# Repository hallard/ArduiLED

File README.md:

AduiLED
=======

Arduino board for driving addressable RGB LED Strip with added nice features. 

Check out other projects on my [blog][1]

Detailed Description
====================

Everything is documented on this dedicated [post][2]

[1]: http://hallard.me
[2]: http://hallard.me/arduiled/

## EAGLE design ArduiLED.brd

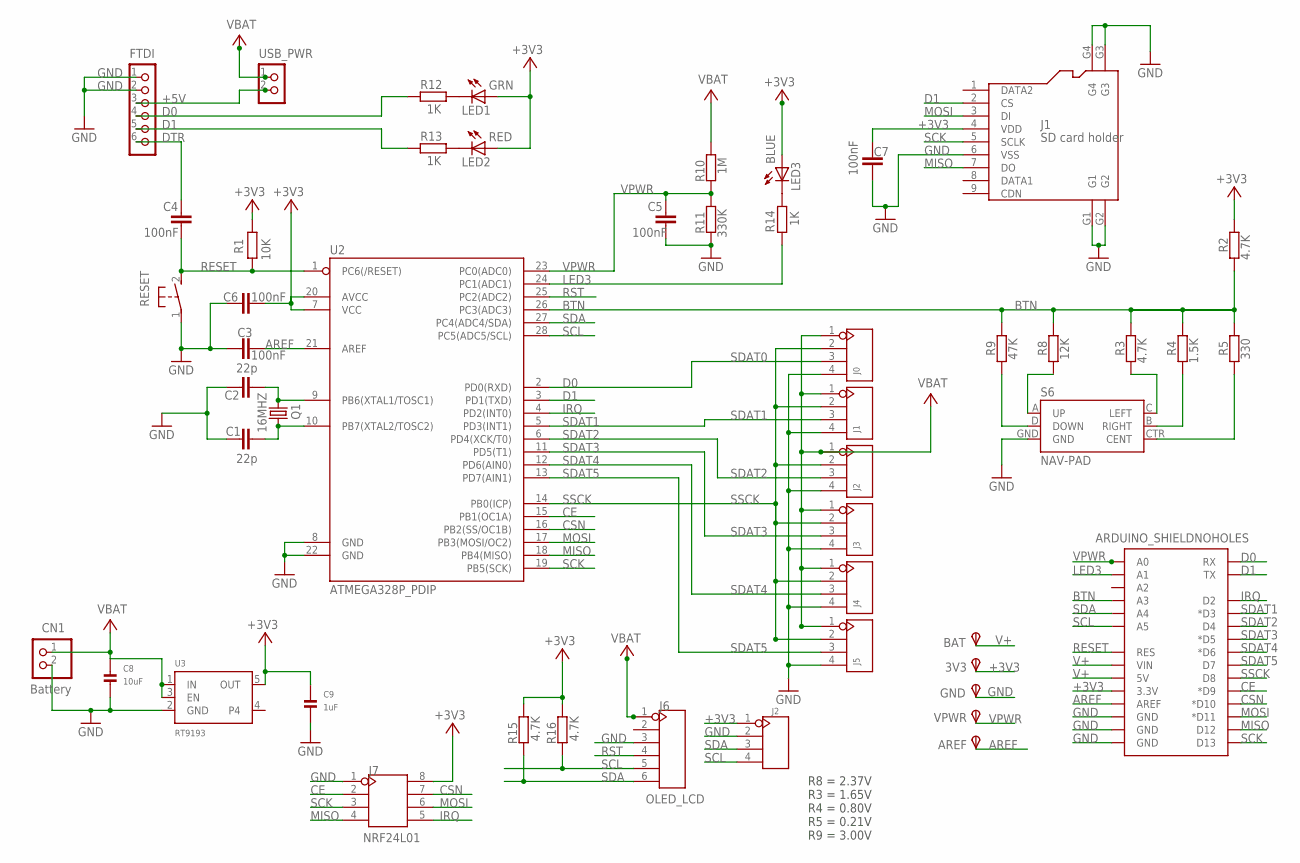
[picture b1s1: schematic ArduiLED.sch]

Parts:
3V3: TPSPAD1-13; P1-13
AREF: TPSPAD1-13; P1-13
BAT: TPSPAD1-13; P1-13
BRA: J2; 4P-2.54-80/40MIL
BRAS: J3; 4P-2.54-80/40MIL
C1, C2: 22p; C0805K
C3, C5, C6, C7: 100nF; C0805K
C4: 100nF; C0805
C8: 10uF; 0805
C9: 1uF; 0805
CN1: Battery; JST-PH-2-SMT-RA
D7: J5; 4P-2.54-80/40MIL
FTDI: CON_HEADER_1X06-PTH-RIGHT-ANGLED; M1X6_MALE_RIGHT_ANGLED
GND: TPSPAD1-13; P1-13
J1: SD card holder; 9P-SMD-W/-RING
J2: HEADER-4P-65/35MIL; 4P-65/35MIL
J6: OLED_LCD; 6P-2.54-65/35MIL
J7: NRF24L01; 2X4P-2.54
JAMB: J4; 4P-2.54-80/40MIL
LED1: GRN; LED-805
LED2: RED; LED-805
LED3: BLUE; LED-805
Q1: 16MHZ; HC49U-V
R1: 10K; M0805
R2, R3, R15, R16: 4.7K; M0805
R4: 1.5K; M0805
R5: 330; M0805
R8: 12K; M0805
R9: 47K; M0805
R10: 1M; M0805
R11: 330K; M0805
R12, R13, R14: 1K; M0805
RESET: DTSM-3
S6: NAV-PAD; JOYSTICK_MINI
TETE: J0; 4P-2.54-80/40MIL
TRONC: J1; 4P-2.54-80/40MIL
U1: ARDUINO_SHIELDNOHOLES; DUEMILANOVE_SHIELD_NOHOLES
U2: ATMEGA328P_PDIP; DIL28-3
U3: RT9193; SOT23-5
USB_PWR: CON_HEADER_1X02-PTH; M1X2
VPWR: TPSPAD1-13; P1-13

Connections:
+3V3: 3V3.TP, C6.2, C7.1, C9.1, J1.4 (VDD), J2.1, J7.8, LED1.A, LED2.A, LED3.A, R1.1, R2.1, R15.1, R16.1, U1.3.3V, U2.7 (VCC), U2.20 (AVCC), U3.5 (OUT)
+5V: FTDI.3, USB_PWR.2
AREF: AREF.TP, C3.1, U1.AREF, U2.21 (AREF)
BTN: R2.2, R3.1, R4.1, R5.1, R8.1, R9.1, U1.A3, U2.26 (PC3(ADC3))
CE: J7.2, U1.D9 (*D9), U2.15 (PB1(OC1A))
CSN: J7.7, U1.D10 (*D10), U2.16 (PB2(SS/OC1B))
D0: FTDI.4, R12.1, TETE.3, U1.RX, U2.2 (PD0(RXD))
D1: FTDI.5, J1.2 (CS), R13.1, U1.TX, U2.3 (PD1(TXD))
DTR: C4.1, FTDI.6
GND: BRA.4, BRAS.4, C1.1, C2.1, C3.2, C5.2, C6.1, C7.2, C8.2, C9.2, CN1.2 (1), D7.4, FTDI.1, FTDI.2, GND.TP, J1.6 (VSS), J1.G1, J1.G2, J1.G3, J1.G4, J2.2, J6.3, J7.1, JAMB.4, R11.2, RESET.1, S6.GND, TETE.4, TRONC.4, U1.GND@0 (GND), U1.GND@1 (GND), U1.GND@2 (GND), U2.8 (GND), U2.22 (GND), U3.2 (GND)
IRQ: J7.5, U1.D2, U2.4 (PD2(INT0))
LED3: R14.1, U1.A1, U2.24 (PC1(ADC1))
MISO: J1.7 (DO), J7.4, U1.D12, U2.18 (PB4(MISO))
MOSI: J1.3 (DI), J7.6, U1.D11 (*D11), U2.17 (PB3(MOSI/OC2))
unnamed: C2.2, Q1.2, U2.9 (PB6(XTAL1/TOSC1))
unnamed: C1.2, Q1.1, U2.10 (PB7(XTAL2/TOSC2))
unnamed: R8.2, S6.A (UP)
unnamed: LED1.C, R12.2
unnamed: R3.2, S6.C (LEFT)
unnamed: LED2.C, R13.2
unnamed: LED3.C, R14.2
unnamed: R4.2, S6.B (RIGHT)
unnamed: R5.2, S6.CTR (CENT)
unnamed: R9.2, S6.D (DOWN)
RESET: C4.2, R1.2, RESET.2, U1.RES, U2.1 (PC6(/RESET))
RST: J6.4, U2.25 (PC2(ADC2))
SCK: J1.5 (SCLK), J7.3, U1.D13, U2.19 (PB5(SCK))
SCL: J2.4, J6.5, R16.2, U1.A5, U2.28 (PC5(ADC5/SCL))
SDA: J2.3, J6.6, R15.2, U1.A4, U2.27 (PC4(ADC4/SDA))
SDAT1: TRONC.3, U1.D3 (*D3), U2.5 (PD3(INT1))
SDAT2: BRA.3, U1.D4, U2.6 (PD4(XCK/T0))
SDAT3: BRAS.3, U1.D5 (*D5), U2.11 (PD5(T1))
SDAT4: JAMB.3, U1.D6 (*D6), U2.12 (PD6(AIN0))
SDAT5: D7.3, U1.D7, U2.13 (PD7(AIN1))
SSCK: BRA.2, BRAS.2, D7.2, JAMB.2, TETE.2, TRONC.2, U1.D8, U2.14 (PB0(ICP))
V+: BAT.TP, BRA.1, BRAS.1, C8.1, CN1.1 (2), D7.1, J6.1, JAMB.1, R10.1, TETE.1, TRONC.1, U1.5V, U1.VIN, U3.1 (IN), U3.3 (EN), USB_PWR.1
VPWR: C5.1, R10.2, R11.1, U1.A0, U2.23 (PC0(ADC0)), VPWR.TP

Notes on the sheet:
SDAT0
R8 = 2.37V R3 = 1.65V R4 = 0.80V R5 = 0.21V R9 = 3.00V

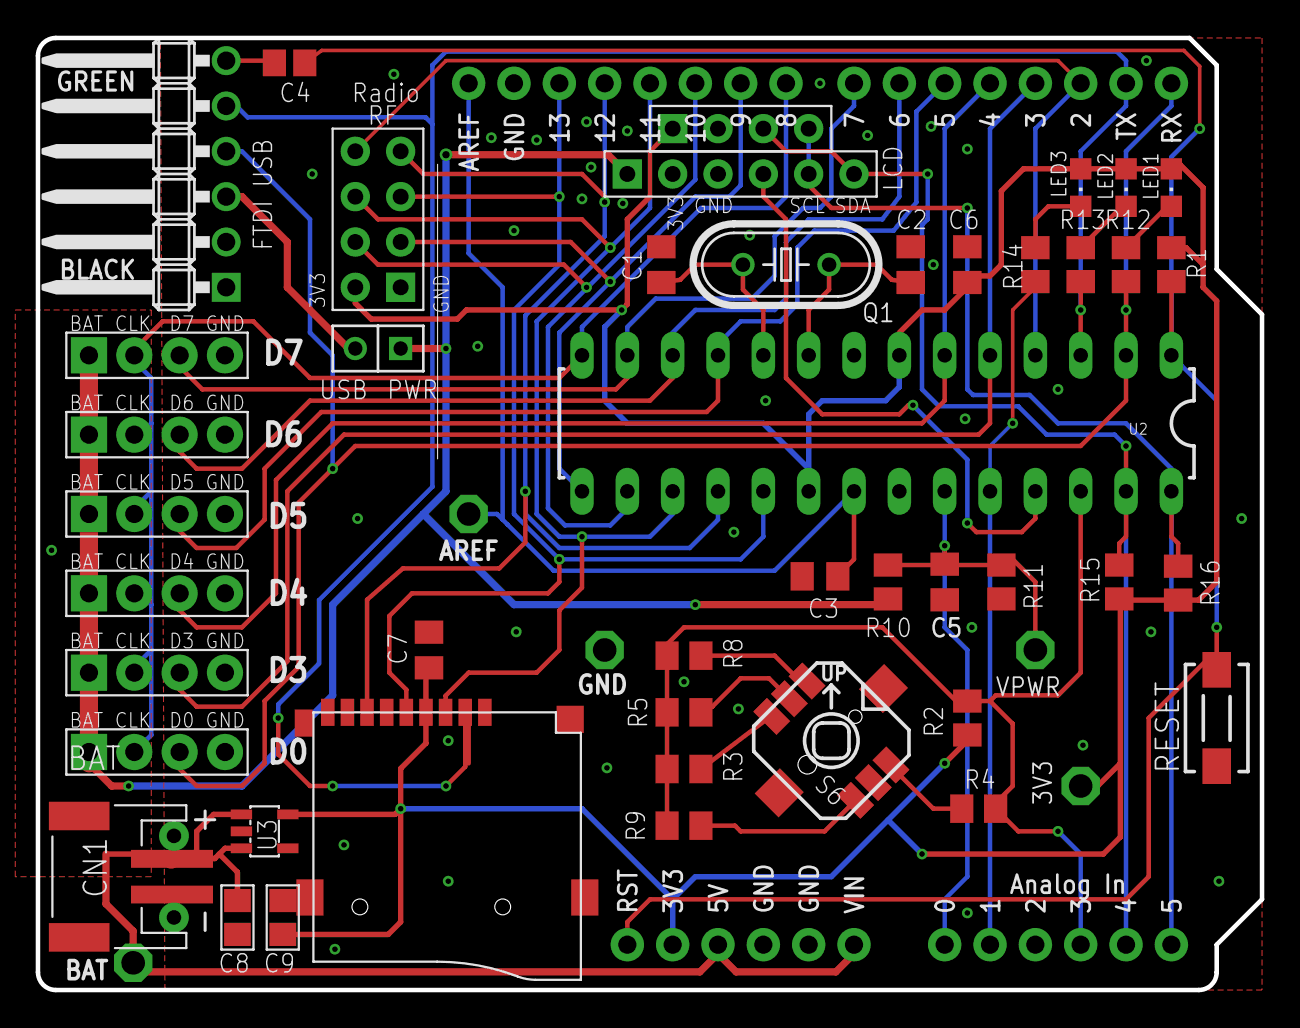
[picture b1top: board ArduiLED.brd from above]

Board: 2 copper layers, 68.6 x 53.3 mm, 50 parts (0 on the bottom side), 37 nets.

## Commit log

2013-09-26 Creation
    Creation

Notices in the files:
parts and their libraries:
SparkFun-Boards: Licensing: CC v3.0 Share-Alike You are welcome to use this library for commercial purposes.
